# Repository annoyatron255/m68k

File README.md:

# m68k
A [Motorola 68000](https://en.wikipedia.org/wiki/Motorola_68000) computer. It uses a Lattice FPGA to control the CPU and interface with the peripherals. It is designed to be standalone, with a PS/2 port for input and a VGA port for display output. 
## Contributors
* [Avery Bartnik](https://github.com/Jythonscript)
  * [Assembly Programming](https://github.com/annoyatron255/m68k/blob/master/src/init.s)
  * README
* [Erik Duxstad](https://github.com/eduxstad)
  * Schematic
  * PCB Layout
  * Ordering PCB
* [Jack Sweeney](https://github.com/annoyatron255)
  * Schematic
  * Assembly Programming
  * FPGA Verilog
  * Simulation
* [Michael Wagner](https://github.com/MDW01)
  * Schematic
  * PCB Layout
  * Ordering Parts
## What We Did
1. Design schematic for 68000 computer
2. Design and layout the PCB
3. Order the PCB and parts
4. Wrote Verilog HDL for the FPGA
5. Set up a RTL simulator for the whole computer design
6. Wrote an assembly program in the simulator that displays text using the serial port
## What We Will Do
1. Solder the parts to the PCB
2. Synthesize the verilog and flash to SPI Flash to configure FPGA
3. Interface with the board via the serial port
4. Run programs on real hardware!
## Long-Term Improvements
1. Enable on-board SRAM
2. Configure toolchain to allow for C programming
3. Add scheduling interrupt
4. Install Linux
5. Set up VGA peripheral
6. Set up PS/2 peripheral
7. Set up SD Card peripheral
8. Make MMU on FPGA for Linux
## Gallery
### PCB

### PCB Layout 

### FPGA

### SRAM

### Schematic

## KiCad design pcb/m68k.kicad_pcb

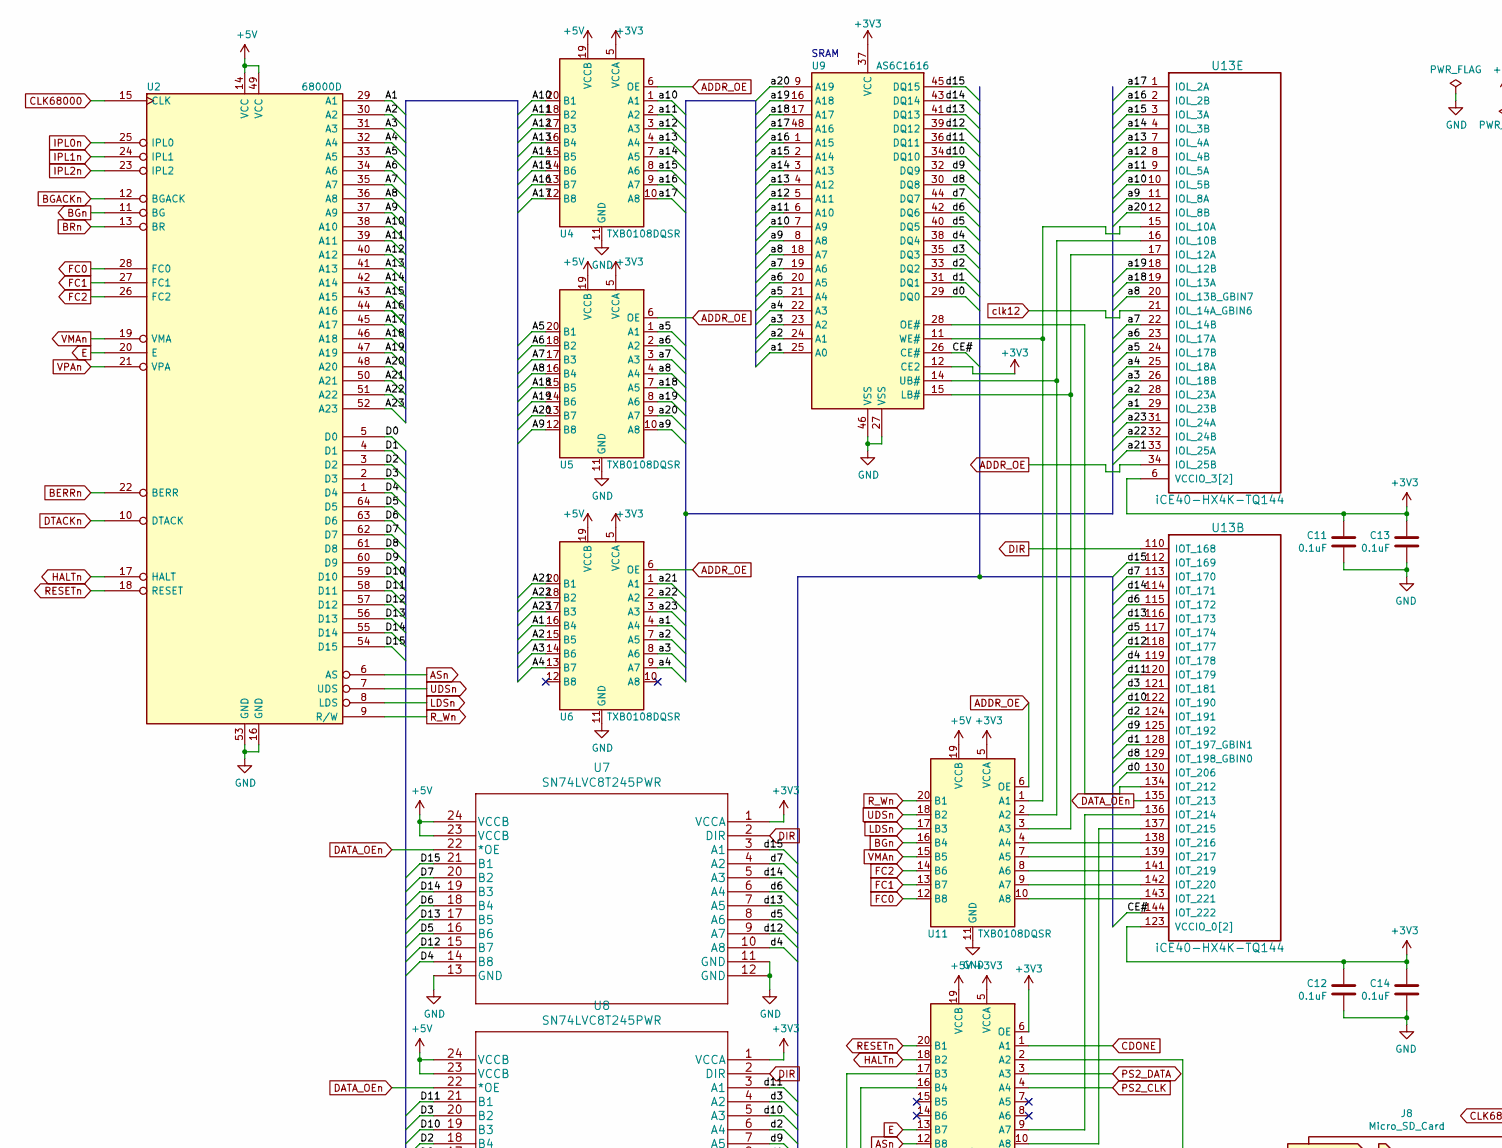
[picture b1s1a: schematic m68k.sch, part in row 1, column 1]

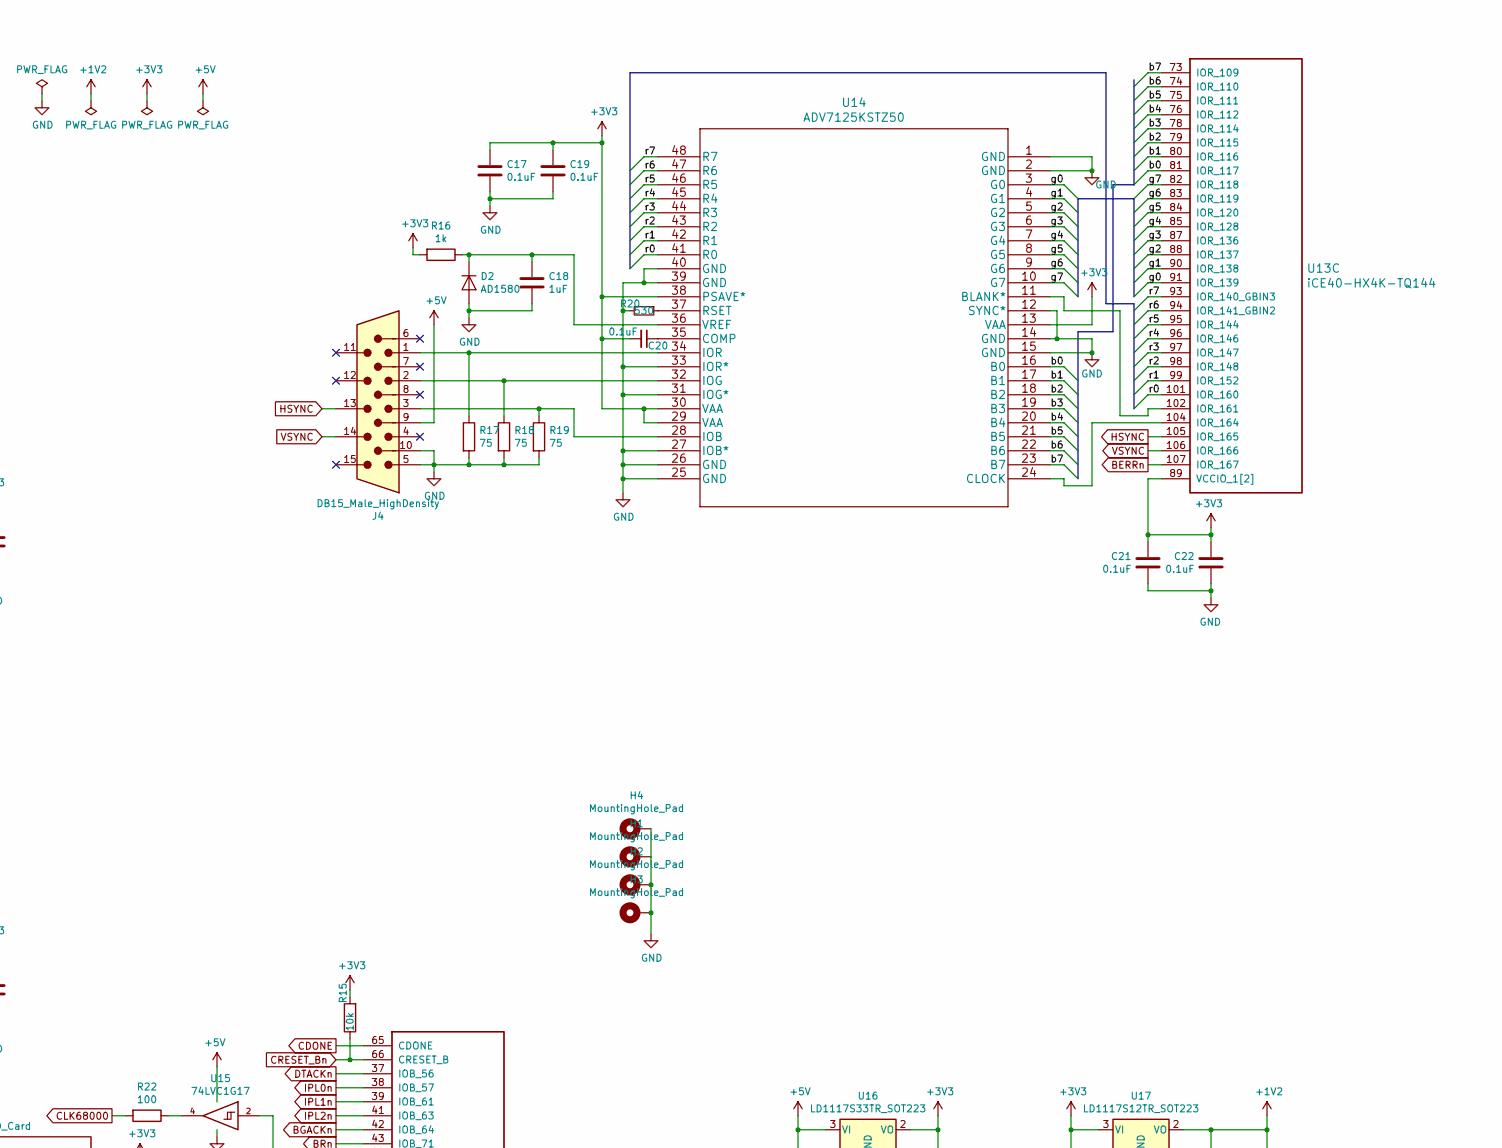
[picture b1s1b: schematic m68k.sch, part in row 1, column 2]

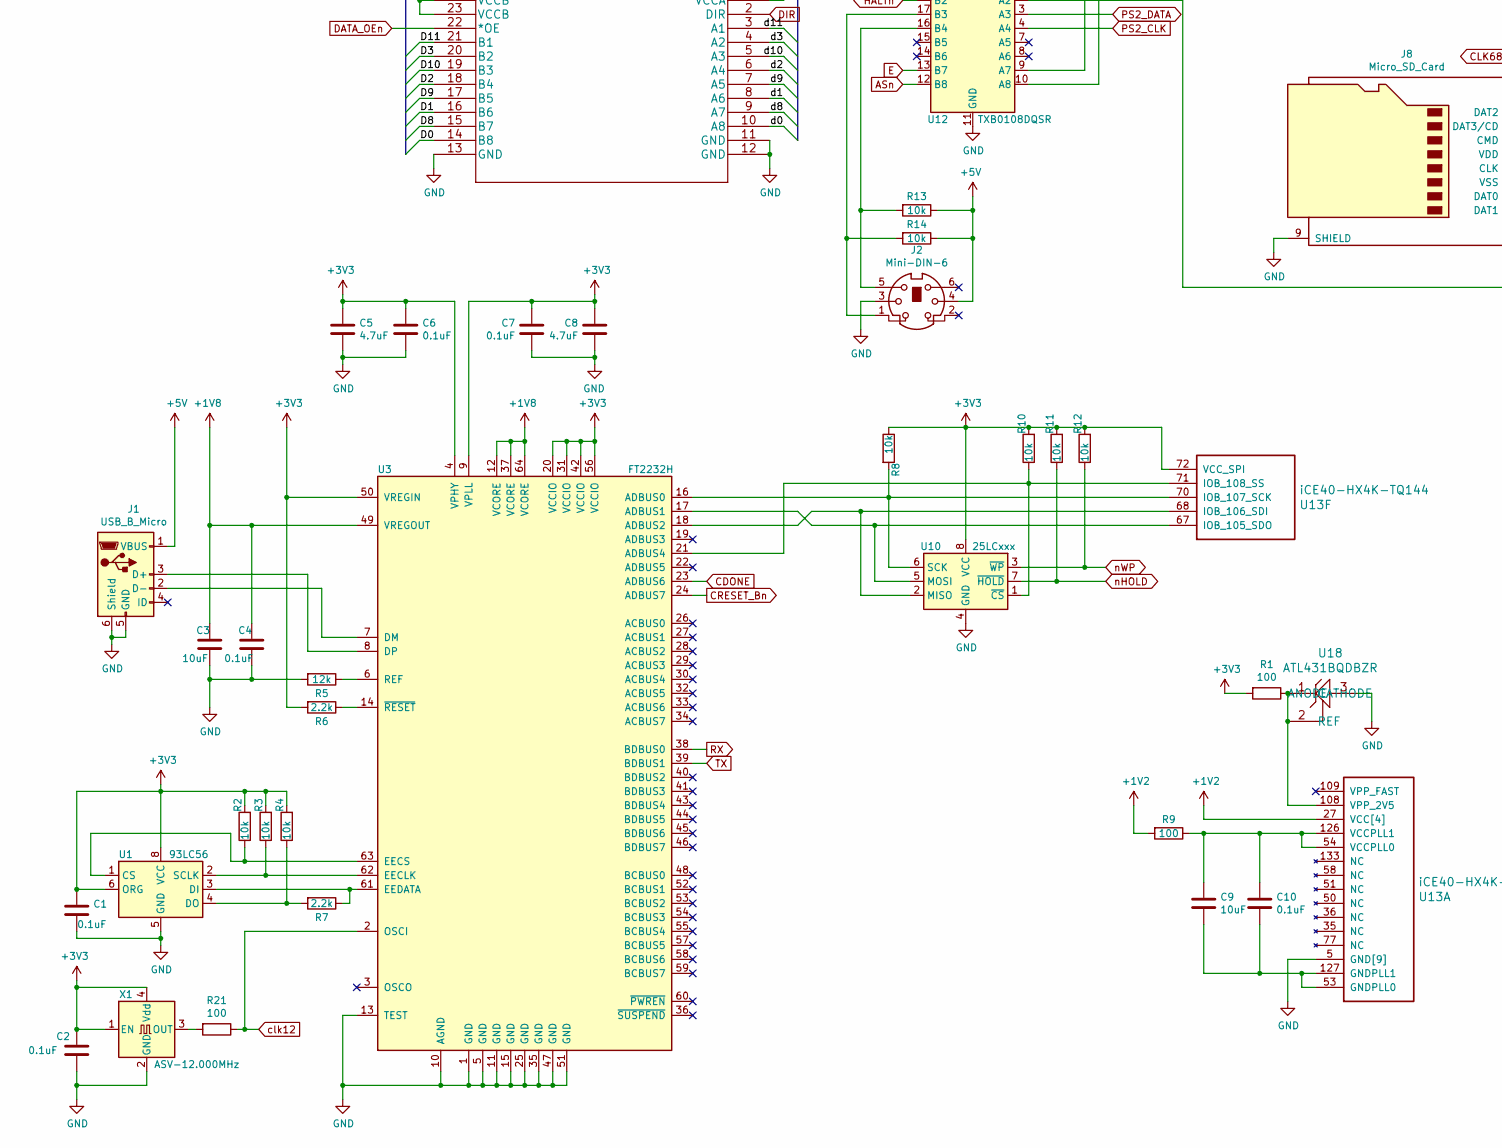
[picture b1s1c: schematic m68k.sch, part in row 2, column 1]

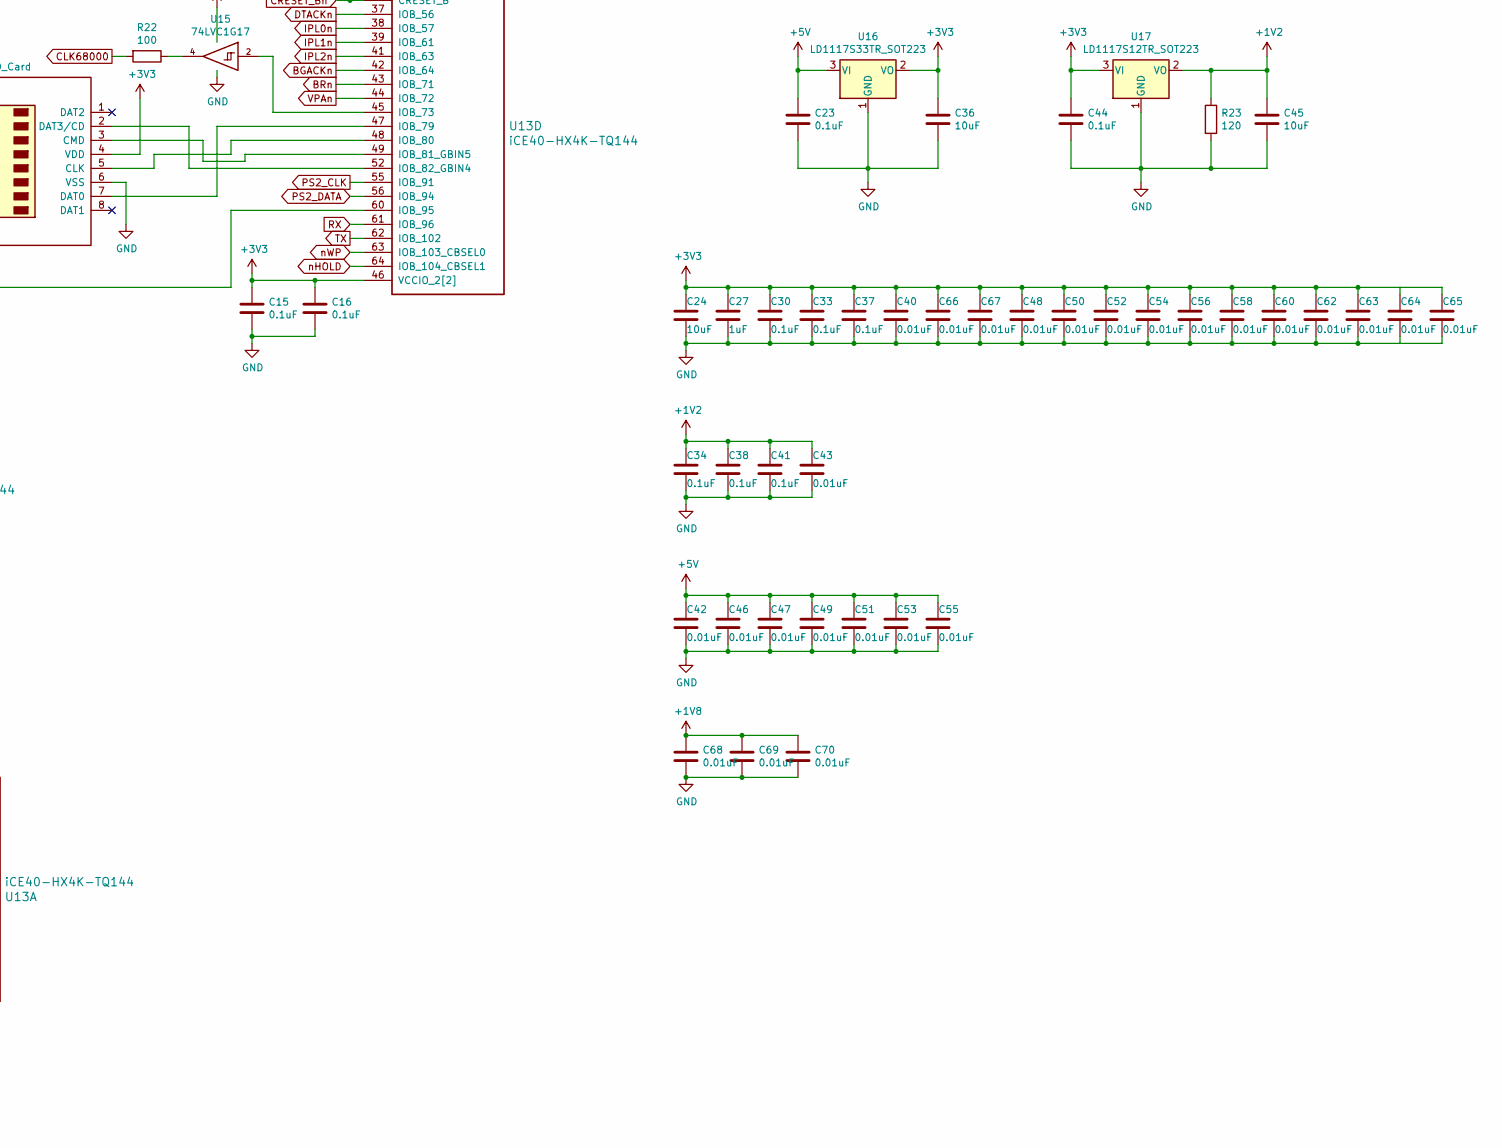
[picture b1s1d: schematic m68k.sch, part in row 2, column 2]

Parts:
C1, C2, C4, C6, C7, C10, C11, C12, C13, C14, C15, C16, C17, C19, C20, C21, C22, C23, C30, C33, C34, C37, C38, C41, C44: 0.1uF; C_0603_1608Metric
C3, C9, C24, C36, C45: 10uF; C_0603_1608Metric
C5, C8: 4.7uF; C_0603_1608Metric
C18, C27: 1uF; C_0603_1608Metric
C40, C42, C43, C46, C47, C48, C49, C50, C51, C52, C53, C54, C55, C56, C58, C60, C62, C63, C64, C65, C66, C67, C68, C69, C70: 0.01uF; C_0603_1608Metric
D2: AD1580; SOT-23
H1, H2, H3, H4: MountingHole_Pad; MountingHole_2.5mm_Pad
J1: USB_B_Micro; USB_Micro-B
J2: Mini-DIN-6; CUI_MD-60S
J4: DB15_Male_HighDensity; DSUB-15-HD_Female_Horizontal_P2.29x1.98mm_EdgePinOffset3.03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
J8: Micro_SD_Card; microSD_HC_Hirose_DM3AT-SF-PEJM5
R1, R9, R21, R22: 100; R_0603_1608Metric
R2, R3, R4, R8, R10, R11, R12, R13, R14, R15: 10k; R_0603_1608Metric
R5: 12k; R_0603_1608Metric
R6, R7: 2.2k; R_0603_1608Metric
R16: 1k; R_0603_1608Metric
R17, R18, R19: 75; R_0603_1608Metric
R20: 530; R_0603_1608Metric
R23: 120; R_0603_1608Metric
U1: 93LC56; SOIC-8_3.9x4.9mm_P1.27mm
U2: 68000D; DIP-64_W22.86mm_Socket_LongPads
U3: FT2232H; LQFP-64_10x10mm_P0.5mm
U4, U5, U6, U11, U12: TXB0108DQSR; USON-20_2x4mm_P0.4mm
U7, U8: SN74LVC8T245PWR; TSSOP-24_4.4x7.8mm_P0.65mm
U9: AS6C1616; TSOP-I-48_18.4x12mm_P0.5mm
U10: 25LCxxx; SOIC-8_3.9x4.9mm_P1.27mm
U13: iCE40-HX4K-TQ144; TQFP-144_20x20mm_P0.5mm
U14: ADV7125KSTZ50; LQFP-48_7x7mm_P0.5mm
U15: 74LVC1G17; SOT-23-5
U16: LD1117S33TR_SOT223; SOT-223-3_TabPin2
U17: LD1117S12TR_SOT223; SOT-223-3_TabPin2
U18: ATL431BQDBZR; SOT-23
X1: ASV-12.000MHz; Oscillator_SMD_Abracon_ASV-4Pin_7.0x5.1mm

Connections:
+1V2: C34.1, C38.1, C41.1, C43.1, C45.1, R9.2, R23.1, U13.27 (VCC[4]), U13.40 (VCC[4]), U13.92 (VCC[4]), U13.111 (VCC[4]), U17.2 (VO)
+1V8: C3.1, C4.1, C68.1, C69.1, C70.1, U3.12 (VCORE), U3.37 (VCORE), U3.49 (VREGOUT), U3.64 (VCORE)
+3V3: C1.1, C2.1, C5.1, C6.1, C7.1, C8.1, C11.1, C12.1, C13.1, C14.1, C15.1, C16.1, C17.1, C19.1, C20.2, C21.1, C22.1, C24.1, C27.1, C30.1, C33.1, C36.1, C37.1, C40.1, C44.1, C48.1, C50.1, C52.1, C54.1, C56.1, C58.1, C60.1, C62.1, C63.1, C64.1, C65.1, C66.1, C67.1, J8.4 (VDD), R1.2, R2.2, R3.2, R4.2, R6.2, R8.1, R10.2, R11.2, R12.2, R15.2, R16.2, U1.6 (ORG), U1.8 (VCC), U3.4 (VPHY), U3.9 (VPLL), U3.20 (VCCIO), U3.31 (VCCIO), U3.42 (VCCIO), U3.50 (VREGIN), U3.56 (VCCIO), U4.5 (VCCA), U5.5 (VCCA), U6.5 (VCCA), U7.1 (VCCA), U8.1 (VCCA), U9.12 (CE2), U9.37 (VCC), U10.8 (VCC), U11.5 (VCCA), U12.5 (VCCA), U12.6 (OE), U13.6 (VCCIO_3[2]), U13.30 (VCCIO_3[2]), U13.46 (VCCIO_2[2]), U13.57 (VCCIO_2[2]), U13.72 (VCC_SPI), U13.89 (VCCIO_1[2]), U13.100 (VCCIO_1[2]), U13.123 (VCCIO_0[2]), U13.131 (VCCIO_0[2]), U14.13 (VAA), U14.29 (VAA), U14.30 (VAA), U14.38 (PSAVE*), U16.2 (VO), U17.3 (VI), X1.1 (EN), X1.4 (Vdd)
+5V: C23.1, C42.1, C46.1, C47.1, C49.1, C51.1, C53.1, C55.1, J1.1 (VBUS), J2.4, J4.9, R13.1, R14.1, U2.14 (VCC), U2.49 (VCC), U4.19 (VCCB), U5.19 (VCCB), U6.19 (VCCB), U7.23 (VCCB), U7.24 (VCCB), U8.23 (VCCB), U8.24 (VCCB), U11.19 (VCCB), U12.19 (VCCB), U15.5 (VCC), U16.3 (VI)
/A1: U2.29 (A1), U6.16 (B4)
/A2: U2.30 (A2), U6.15 (B5)
/A3: U2.31 (A3), U6.14 (B6)
/A4: U2.32 (A4), U6.13 (B7)
/A5: U2.33 (A5), U5.20 (B1)
/A6: U2.34 (A6), U5.18 (B2)
/A7: U2.35 (A7), U5.17 (B3)
/A8: U2.36 (A8), U5.16 (B4)
/A9: U2.37 (A9), U5.12 (B8)
/A10: U2.38 (A10), U4.20 (B1)
/A11: U2.39 (A11), U4.18 (B2)
/A12: U2.40 (A12), U4.17 (B3)
/A13: U2.41 (A13), U4.16 (B4)
/A14: U2.42 (A14), U4.15 (B5)
/A15: U2.43 (A15), U4.14 (B6)
/A16: U2.44 (A16), U4.13 (B7)
/A17: U2.45 (A17), U4.12 (B8)
/A18: U2.46 (A18), U5.15 (B5)
/A19: U2.47 (A19), U5.14 (B6)
/A20: U2.48 (A20), U5.13 (B7)
/A21: U2.50 (A21), U6.20 (B1)
/A22: U2.51 (A22), U6.18 (B2)
/A23: U2.52 (A23), U6.17 (B3)
/CE#: U9.26 (CE#), U13.144 (IOT_222)
/D0: U2.5 (D0), U8.14 (B8)
/D1: U2.4 (D1), U8.16 (B6)
/D2: U2.3 (D2), U8.18 (B4)
/D3: U2.2 (D3), U8.20 (B2)
/D4: U2.1 (D4), U7.14 (B8)
/D5: U2.64 (D5), U7.16 (B6)
/D6: U2.63 (D6), U7.18 (B4)
/D7: U2.62 (D7), U7.20 (B2)
/D8: U2.61 (D8), U8.15 (B7)
/D9: U2.60 (D9), U8.17 (B5)
/D10: U2.59 (D10), U8.19 (B3)
/D11: U2.58 (D11), U8.21 (B1)
/D12: U2.57 (D12), U7.15 (B7)
/D13: U2.56 (D13), U7.17 (B5)
/D14: U2.55 (D14), U7.19 (B3)
/D15: U2.54 (D15), U7.21 (B1)
/a1: U6.4 (A4), U9.25 (A0), U13.29 (IOL_23B)
/a2: U6.7 (A5), U9.24 (A1), U13.28 (IOL_23A)
/a3: U6.8 (A6), U9.23 (A2), U13.26 (IOL_18B)
/a4: U6.9 (A7), U9.22 (A3), U13.25 (IOL_18A)
/a5: U5.1 (A1), U9.21 (A4), U13.24 (IOL_17B)
/a6: U5.2 (A2), U9.20 (A5), U13.23 (IOL_17A)
/a7: U5.3 (A3), U9.19 (A6), U13.22 (IOL_14B)
/a8: U5.4 (A4), U9.18 (A7), U13.20 (IOL_13B_GBIN7)
/a9: U5.10 (A8), U9.8 (A8), U13.11 (IOL_8A)
/a10: U4.1 (A1), U9.7 (A9), U13.10 (IOL_5B)
/a11: U4.2 (A2), U9.6 (A10), U13.9 (IOL_5A)
/a12: U4.3 (A3), U9.5 (A11), U13.8 (IOL_4B)
/a13: U4.4 (A4), U9.4 (A12), U13.7 (IOL_4A)
/a14: U4.7 (A5), U9.3 (A13), U13.4 (IOL_3B)
/a15: U4.8 (A6), U9.2 (A14), U13.3 (IOL_3A)
/a16: U4.9 (A7), U9.1 (A15), U13.2 (IOL_2B)
/a17: U4.10 (A8), U9.48 (A16), U13.1 (IOL_2A)
/a18: U5.7 (A5), U9.17 (A17), U13.19 (IOL_13A)
/a19: U5.8 (A6), U9.16 (A18), U13.18 (IOL_12B)
/a20: U5.9 (A7), U9.9 (A19), U13.12 (IOL_8B)
/a21: U6.1 (A1), U13.33 (IOL_25A)
/a22: U6.2 (A2), U13.32 (IOL_24B)
/a23: U6.3 (A3), U13.31 (IOL_24A)
/b0: U13.81 (IOR_117), U14.16 (B0)
/b1: U13.80 (IOR_116), U14.17 (B1)
/b2: U13.79 (IOR_115), U14.18 (B2)
/b3: U13.78 (IOR_114), U14.19 (B3)
/b4: U13.76 (IOR_112), U14.20 (B4)
/b5: U13.75 (IOR_111), U14.21 (B5)
/b6: U13.74 (IOR_110), U14.22 (B6)
/b7: U13.73 (IOR_109), U14.23 (B7)
/d0: U8.10 (A8), U9.29 (DQ0), U13.130 (IOT_206)
/d1: U8.8 (A6), U9.31 (DQ1), U13.128 (IOT_197_GBIN1)
/d2: U8.6 (A4), U9.33 (DQ2), U13.124 (IOT_191)
/d3: U8.4 (A2), U9.35 (DQ3), U13.121 (IOT_181)
/d4: U7.10 (A8), U9.38 (DQ4), U13.119 (IOT_178)
/d5: U7.8 (A6), U9.40 (DQ5), U13.117 (IOT_174)
/d6: U7.6 (A4), U9.42 (DQ6), U13.115 (IOT_172)
/d7: U7.4 (A2), U9.44 (DQ7), U13.113 (IOT_170)
/d8: U8.9 (A7), U9.30 (DQ8), U13.129 (IOT_198_GBIN0)
/d9: U8.7 (A5), U9.32 (DQ9), U13.125 (IOT_192)
/d10: U8.5 (A3), U9.34 (DQ10), U13.122 (IOT_190)
/d11: U8.3 (A1), U9.36 (DQ11), U13.120 (IOT_179)
/d12: U7.9 (A7), U9.39 (DQ12), U13.118 (IOT_177)
/d13: U7.7 (A5), U9.41 (DQ13), U13.116 (IOT_173)
/d14: U7.5 (A3), U9.43 (DQ14), U13.114 (IOT_171)
/d15: U7.3 (A1), U9.45 (DQ15), U13.112 (IOT_169)
/g0: U13.91 (IOR_139), U14.3 (G0)
/g1: U13.90 (IOR_138), U14.4 (G1)
/g2: U13.88 (IOR_137), U14.5 (G2)
/g3: U13.87 (IOR_136), U14.6 (G3)
/g4: U13.85 (IOR_128), U14.7 (G4)
/g5: U13.84 (IOR_120), U14.8 (G5)
/g6: U13.83 (IOR_119), U14.9 (G6)
/g7: U13.82 (IOR_118), U14.10 (G7)
/r0: U13.101 (IOR_160), U14.41 (R0)
/r1: U13.99 (IOR_152), U14.42 (R1)
/r2: U13.98 (IOR_148), U14.43 (R2)
/r3: U13.97 (IOR_147), U14.44 (R3)
/r4: U13.96 (IOR_146), U14.45 (R4)
/r5: U13.95 (IOR_144), U14.46 (R5)
/r6: U13.94 (IOR_141_GBIN2), U14.47 (R6)
/r7: U13.93 (IOR_140_GBIN3), U14.48 (R7)
ADDR_OE: U4.6 (OE), U5.6 (OE), U6.6 (OE), U11.6 (OE), U13.34 (IOL_25B)
ASn: U2.6 (AS), U12.12 (B8)
BERRn: U2.22 (BERR), U13.107 (IOR_167)
BGACKn: U2.12 (BGACK), U13.42 (IOB_64)
BGn: U2.11 (BG), U11.16 (B4)
BRn: U2.13 (BR), U13.43 (IOB_71)
CDONE: U3.23 (ADBUS6), U12.1 (A1), U13.65 (CDONE)
CLK68000: R22.2, U2.15 (CLK)
CRESET_Bn: R15.1, U3.24 (ADBUS7), U13.66 (CRESET_B)
DATA_OEn: U7.22 (*OE), U8.22 (*OE), U13.135 (IOT_213)
DIR: U7.2 (DIR), U8.2 (DIR), U13.110 (IOT_168)
DTACKn: U2.10 (DTACK), U13.37 (IOB_56)
E: U2.20 (E), U12.13 (B7)
FC0: U2.28 (FC0), U11.12 (B8)
FC1: U2.27 (FC1), U11.13 (B7)
FC2: U2.26 (FC2), U11.14 (B6)
GND: C1.2, C2.2, C3.2, C4.2, C5.2, C6.2, C7.2, C8.2, C11.2, C12.2, C13.2, C14.2, C15.2, C16.2, C17.2, C18.2, C19.2, C21.2, C22.2, C23.2, C24.2, C27.2, C30.2, C33.2, C34.2, C36.2, C37.2, C38.2, C40.2, C41.2, C42.2, C43.2, C44.2, C45.2, C46.2, C47.2, C48.2, C49.2, C50.2, C51.2, C52.2, C53.2, C54.2, C55.2, C56.2, C58.2, C60.2, C62.2, C63.2, C64.2, C65.2, C66.2, C67.2, C68.2, C69.2, C70.2, D2.2 (A), H1.1, H2.1, H3.1, H4.1, J1.5 (GND), J1.6 (Shield), J2.3, J4.5, J4.10, J8.6 (VSS), J8.9 (SHIELD), R5.2, R17.2, R18.2, R19.2, R20.2, R23.2, U1.5 (GND), U2.16 (GND), U2.53 (GND), U3.1 (GND), U3.5 (GND), U3.10 (AGND), U3.11 (GND), U3.13 (TEST), U3.15 (GND), U3.25 (GND), U3.35 (GND), U3.47 (GND), U3.51 (GND), U4.11 (GND), U5.11 (GND), U6.11 (GND), U7.11 (GND), U7.12 (GND), U7.13 (GND), U8.11 (GND), U8.12 (GND), U8.13 (GND), U9.27 (VSS), U9.46 (VSS), U10.4 (GND), U11.11 (GND), U12.11 (GND), U13.5 (GND[9]), U13.13 (GND[9]), U13.14 (GND[9]), U13.59 (GND[9]), U13.69 (GND[9]), U13.86 (GND[9]), U13.103 (GND[9]), U13.132 (GND[9]), U13.140 (GND[9]), U14.1 (GND), U14.2 (GND), U14.12 (SYNC*), U14.14 (GND), U14.15 (GND), U14.25 (GND), U14.26 (GND), U14.27 (IOB*), U14.31 (IOG*), U14.33 (IOR*), U14.39 (GND), U14.40 (GND), U15.3 (GND), U16.1 (GND), U17.1 (GND), U18.3 (ANODE), X1.2 (GND)
HALTn: U2.17 (HALT), U12.18 (B2)
HSYNC: J4.13, U13.105 (IOR_165)
IPL0n: U2.25 (IPL0), U13.38 (IOB_57)
IPL1n: U2.24 (IPL1), U13.39 (IOB_61)
IPL2n: U2.23 (IPL2), U13.41 (IOB_63)
LDSn: U2.8 (LDS), U11.17 (B3)
unnamed: C9.1, C10.1, R9.1, U13.54 (VCCPLL0), U13.126 (VCCPLL1)
unnamed: C9.2, C10.2, U13.53 (GNDPLL0), U13.127 (GNDPLL1)
unnamed: C18.1, D2.1 (K), R16.1, U14.36 (VREF)
unnamed: C20.1, U14.35 (COMP)
unnamed: J1.2 (D-), U3.7 (DM)
unnamed: J1.3 (D+), U3.8 (DP)
unnamed: J2.1, R14.2, U12.17 (B3)
unnamed: J2.5, R13.2, U12.16 (B4)
unnamed: J4.1, R17.1, U14.34 (IOR)
unnamed: J4.2, R18.1, U14.32 (IOG)
unnamed: J4.3, R19.1, U14.28 (IOB)
unnamed: J8.2 (DAT3/CD), U13.52 (IOB_82_GBIN4)
unnamed: J8.3 (CMD), U13.49 (IOB_81_GBIN5)
unnamed: J8.5 (CLK), U13.48 (IOB_80)
unnamed: J8.7 (DAT0), U13.47 (IOB_79)
unnamed: R1.1, U13.108 (VPP_2V5), U18.1 (CATHODE), U18.2 (REF)
unnamed: R2.1, U1.1 (CS), U3.63 (EECS)
unnamed: R3.1, U1.2 (SCLK), U3.62 (EECLK)
unnamed: R4.1, R7.2, U1.4 (DO)
unnamed: R5.1, U3.6 (REF)
unnamed: R6.1, U3.14 (~RESET)
unnamed: R7.1, U1.3 (DI), U3.61 (EEDATA)
unnamed: R8.2, U3.16 (ADBUS0), U10.6 (SCK), U13.70 (IOB_107_SCK)
unnamed: R10.1, U3.21 (ADBUS4), U10.1 (~CS), U13.71 (IOB_108_SS)
unnamed: R20.1, U14.37 (RSET)
unnamed: R21.2, X1.3 (OUT)
unnamed: R22.1, U15.4
unnamed: U3.18 (ADBUS2), U10.2 (MISO), U13.68 (IOB_106_SDI)
unnamed: U3.17 (ADBUS1), U10.5 (MOSI), U13.67 (IOB_105_SDO)
unnamed: U9.11 (WE#), U11.1 (A1), U13.15 (IOL_10A)
unnamed: U9.14 (UB#), U11.2 (A2), U13.16 (IOL_10B)
unnamed: U9.15 (LB#), U11.3 (A3), U13.17 (IOL_12A)
unnamed: U11.4 (A4), U13.138 (IOT_216)
unnamed: U11.7 (A5), U13.139 (IOT_217)
unnamed: U11.8 (A6), U13.141 (IOT_219)
unnamed: U11.9 (A7), U13.142 (IOT_220)
unnamed: U11.10 (A8), U13.143 (IOT_221)
unnamed: U12.2 (A2), U13.60 (IOB_95)
unnamed: U12.9 (A7), U13.136 (IOT_214)
unnamed: U12.10 (A8), U13.137 (IOT_215)
unnamed: U13.45 (IOB_73), U15.2
unnamed: U13.102 (IOR_161), U14.11 (BLANK*)
unnamed: U13.104 (IOR_164), U14.24 (CLOCK)
unnamed: U9.28 (OE#), U13.134 (IOT_212)
PS2_CLK: U12.4 (A4), U13.55 (IOB_91)
PS2_DATA: U12.3 (A3), U13.56 (IOB_94)
RESETn: U2.18 (RESET), U12.20 (B1)
RX: U3.38 (BDBUS0), U13.61 (IOB_96)
R_Wn: U2.9 (R/W), U11.20 (B1)
TX: U3.39 (BDBUS1), U13.62 (IOB_102)
UDSn: U2.7 (UDS), U11.18 (B2)
VMAn: U2.19 (VMA), U11.15 (B5)
VPAn: U2.21 (VPA), U13.44 (IOB_72)
VSYNC: J4.14, U13.106 (IOR_166)
clk12: R21.1, U3.2 (OSCI), U13.21 (IOL_14A_GBIN6)
nHOLD: R11.1, U10.7 (~HOLD), U13.64 (IOB_104_CBSEL1)
nWP: R12.1, U10.3 (~WP), U13.63 (IOB_103_CBSEL0)

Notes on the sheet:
SRAM

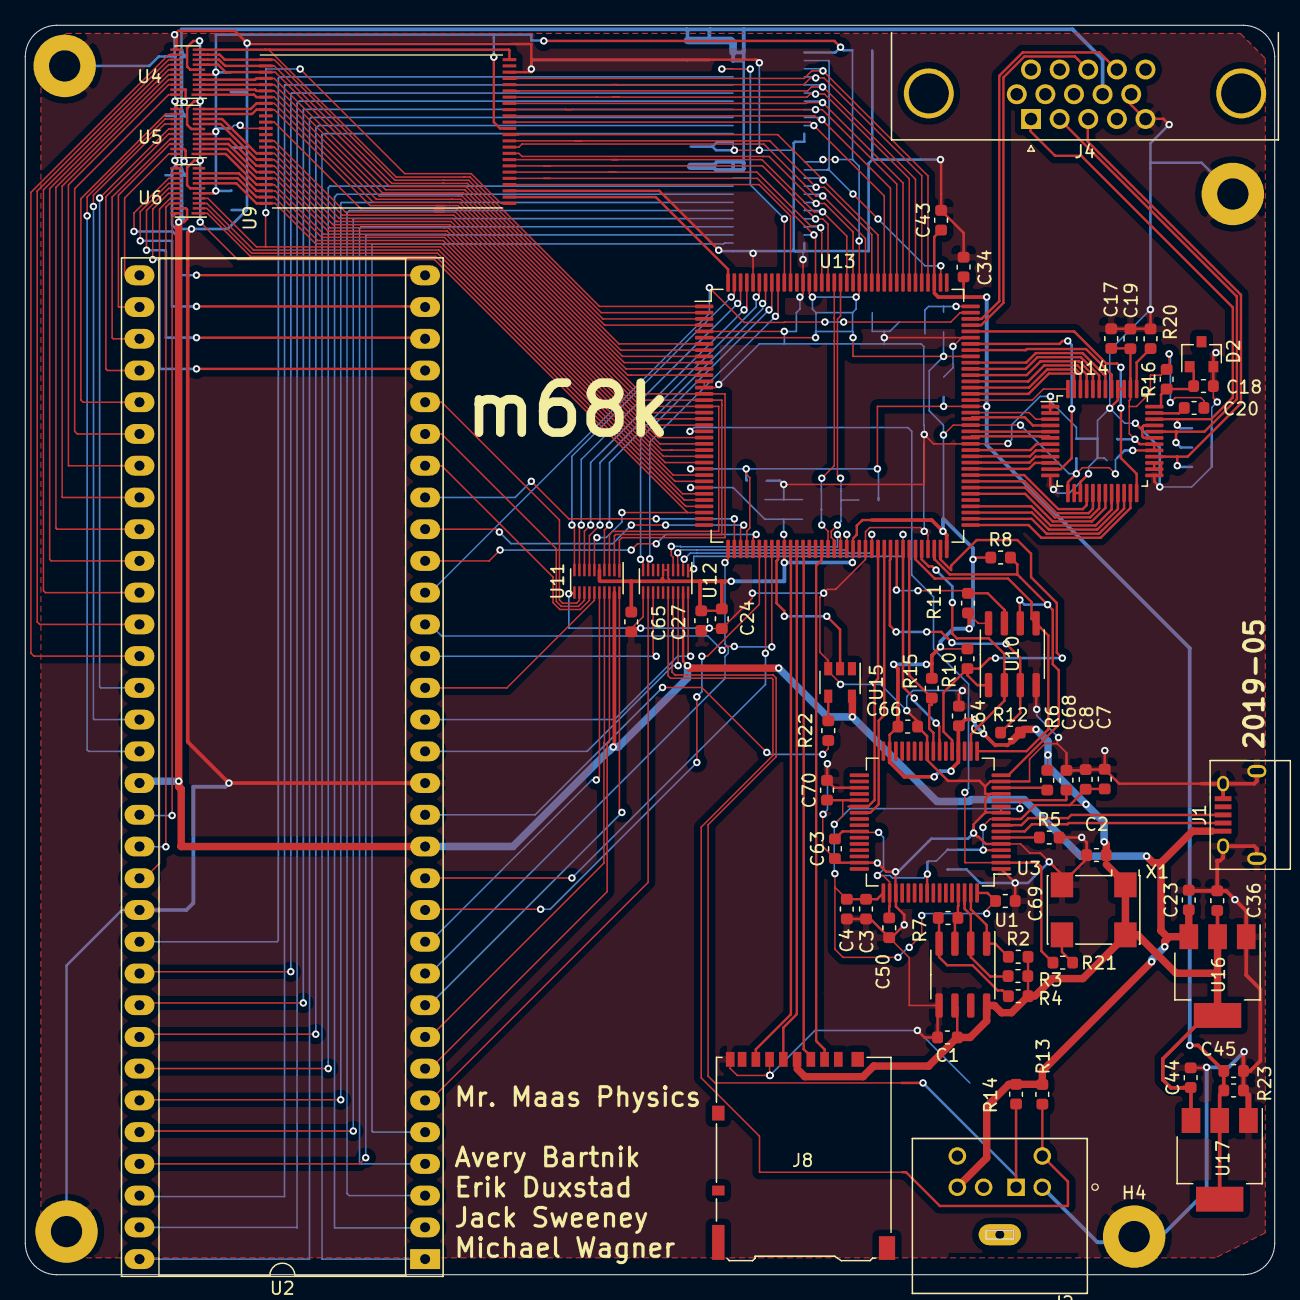
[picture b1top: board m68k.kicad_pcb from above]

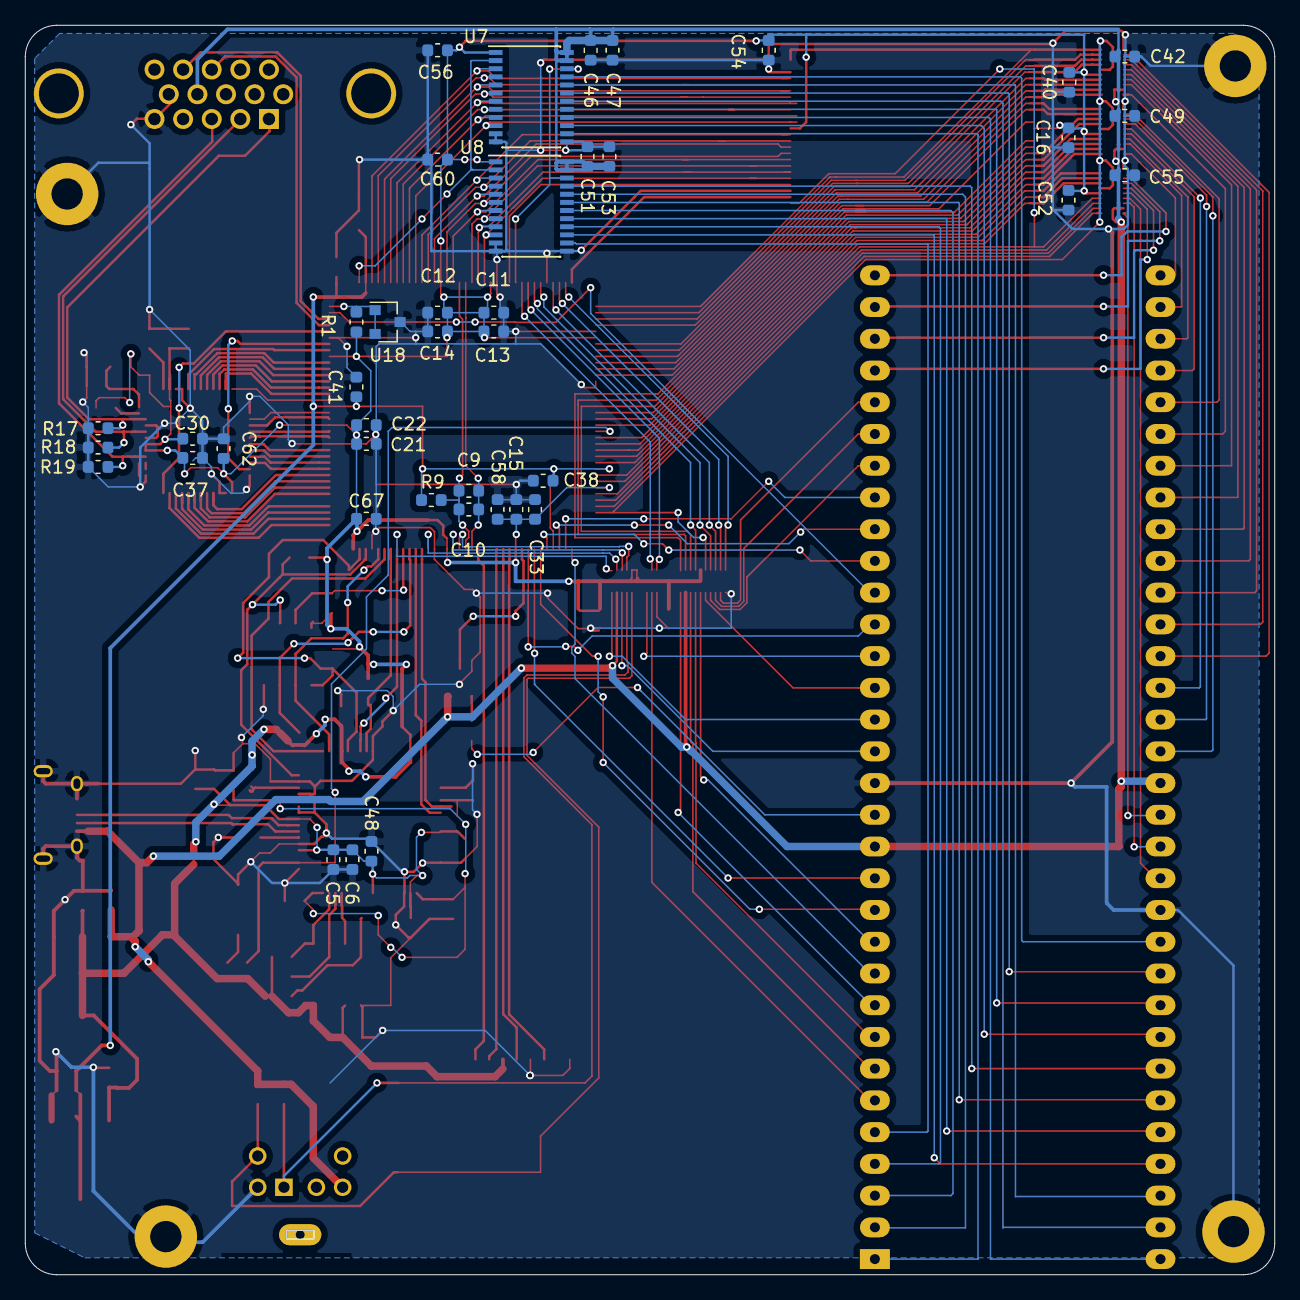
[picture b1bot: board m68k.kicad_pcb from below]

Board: 2 copper layers, 100.0 x 100.0 mm, 110 parts (41 on the bottom side), 187 nets.

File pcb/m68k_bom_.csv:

Component,Description,Value,Footprint,Quantity Per PCB,Digikey,Ordered ,,,
1,Unpolarized capacitor,10000 pF,0603,25,_1276-1132-1-ND_,,,,
2,Unpolarized capacitor,0.1uF,0603,25,_1276-1006-1-ND_,,,,
3,Unpolarized capacitor,10uF,0603,5,_1276-1192-1-ND_,,,,
4,Unpolarized capacitor,1uF,0603,2,1276-1102-1-ND_,,,,
5,Unpolarized capacitor,4.7uF,0603,2,_1276-1044-1-ND_,,,,
6,Diode,AD1580,SOT-23,1,_AD1580ARTZ-REEL7CT-ND_,,,,
7,Micro SD Card Socket,Micro_SD_Card,DM3AT-SF-PEJM5,1,_HR1964CT-ND_,,,,
8,Mini-DIN-6,Mini-DIN-6,CUI_MD-60S,1,_CP-2460-ND_,,,,
9,USB_B_Micro,USB_B_Micro,USB_Micro-B,1,_609-4618-1-ND_,,,,
10,Resistor,100,0603,4,311-100HRCT-ND,,,,
11,Resistor,10k,0603,10,N/A,0,,,
12,Resistor,120,0603,1,311-120HRCT-ND,,,,
13,Resistor,1k,0603,1,N/A,0,,,
14,Resistor,2.2k,0603,3,311-2.20KHRCT-ND,,,,
15,Resistor,530,0603,1,_311-536HRCT-ND_,,,,
16,Resistor,75,0603,3,311-75.0HRCT-ND,,,,
17,"SPI Serial EEPROM, DIP-8/SOIC-8/TSSOP-8",25LCxxx,SOIC-8_3.9x4.9mm_P1.27mm,1,_W25Q128JVSIMCT-ND_,,,,
18,68000D,68000D,DIP-64_W22.86mm_Socket_LongPads,1,N/A,0,,,
19,"Single Schmitt Buffer Gate, Low-Voltage CMOS",74LVC1G17,SOT-23-5,1,_296-35948-1-ND_,,,,
20,"Serial EEPROM, 93 Series, with ORG Pin, 2.5V, DIP-8/SOIC-8",93LC56,SOIC-8_3.9x4.9mm_P1.27mm,1,_93LC56BT-I/SNCT-ND_,,,,
21,,ADV7125KSTZ50,LQFP-48_7x7mm_P0.5mm,1,_ADV7125KSTZ50-ND_,,,,
22,,AS6C1616,TSOP-I-48_18.4x12mm_P0.5mm,1,_1450-1022-ND_,,,,
23,,ATL431BQDBZR,SOT-23,1,_296-44371-1-ND_,,,,
24,"FT2232Hx, Hi Speed Double Channel USB UART/FIFO, LQFP/QFN-64",FT2232H,LQFP-64_10x10mm_P0.5mm,1,_768-1347-ND_,,,,
25,"800mA Fixed Low Drop Positive Voltage Regulator, Fixed Output 1.2V, SOT-223",LD1117S12TR_SOT223,SOT-223-3_TabPin2,1,_497-4240-1-ND_,,,,
26,"800mA Fixed Low Drop Positive Voltage Regulator, Fixed Output 3.3V, SOT-223",LD1117S33TR_SOT223,SOT-223-3_TabPin2,1,_497-1242-1-ND_,,,,
27,,SN74LVC8T245PWR,TSSOP-24_4.4x7.8mm_P0.65mm,2,_296-18593-1-ND_,,,,
28,,TXB0108DQSR,USON-20_2x4mm_P0.4mm,5,_296-27217-1-ND_,,,,
29,,iCE40-HX4K-TQ144,TQFP-144_20x20mm_P0.5mm,1,_220-1572-ND_,,,,
30,"3.3V HCMOS SMD Crystal Clock Oscillator, Abracon",ASV-12.000MHz,Oscillator_SMD_Abracon_ASV-4Pin_7.0x5.1mm,1,_535-9309-1-ND_,,,,

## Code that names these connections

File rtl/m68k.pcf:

set_io clk12 21
set_io CLK68000 45

set_io addr[1] 29
set_io addr[2] 28
set_io addr[3] 26
set_io addr[4] 25
set_io addr[5] 24
set_io addr[6] 23
set_io addr[7] 22
set_io addr[8] 20
set_io addr[9] 11
set_io addr[10] 10
set_io addr[11] 9
set_io addr[12] 8
set_io addr[13] 7
set_io addr[14] 4
set_io addr[15] 3
set_io addr[16] 2
set_io addr[17] 1
set_io addr[18] 19
set_io addr[19] 18
set_io addr[20] 12
set_io addr[21] 33
set_io addr[22] 32
set_io addr[23] 31

set_io data[0] 130
set_io data[1] 128
set_io data[2] 124
set_io data[3] 121
set_io data[4] 119
set_io data[5] 117
set_io data[6] 115
set_io data[7] 113
set_io data[8] 129
set_io data[9] 125
set_io data[10] 122
set_io data[11] 120
set_io data[12] 118
set_io data[13] 116
set_io data[14] 114
set_io data[15] 112

set_io ASn 137
set_io R_Wn 15
set_io UDSn 16
set_io LDSn 17
set_io DTACKn 37

set_io BRn 43
set_io BGn 138
set_io BGACKn 42

set_io IPLn[0] 38
set_io IPLn[1] 39
set_io IPLn[2] 41

set_io FC[0] 143
set_io FC[1] 142
set_io FC[2] 141

set_io E 136
set_io VMAn 139
set_io VPAn 44

set_io BERRn 107
#set_io RESETn
set_io HALTn 60

set_io DATA_OEn 135
set_io ADDR_OE 34
set_io DIR 110

set_io RX 61
set_io TX 62

#set_io [7:0] RX_data
#set_io [7:0] TX_data
#set_io TXE
#set_io TX_read

set_io SRAM_OEn 134
set_io SRAM_CEn 144

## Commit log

2019-05-15 Add KiCAD files
2019-05-16 start schematic
2019-05-16 potential dram schematic
2019-05-17 add rtdi sd and ps2
2019-05-17 Cleanup schematic and fix errors
2019-05-17 add vga dac and start control pins
2019-05-17 Clean-up some signals
2019-05-19 Fix mostly everything
2019-05-19 Fix VBUS voltage
2019-05-19 Add various updates and import to Pcbnew
2019-05-19 Reordered U8 Pins
2019-05-20 Reorder SRAM Pins
2019-05-20 add test points and rearrange pins
    This branch needs to be checked to make sure I didn't mess anything up on the pcb. If so, you can merge it back into erik-dev, otherwise you'll have to update the schem and pcb manually
2019-05-20 Update footprints (Mini DIN for PS/2 still missing)
2019-05-20 start pcb layout
2019-05-20 update io
2019-05-20 Added board outline
2019-05-20 arrange pcb
2019-05-20 switch to micro sd
2019-05-20 fix vga pinout
2019-05-20 add ps/2
2019-05-20 change to 200x100
2019-05-20 Add initial files for verilog
2019-05-21 continue pcb layout
2019-05-21 add autorouter attempt
2019-05-21 routing
2019-05-21 continue routing
2019-05-21 Add initial build utils for rom
2019-05-21 Add darwin tools and update Makefile
2019-05-21 good luck michael
2019-05-21 Add base verilog (untested)
2019-05-22 SAVE ME -Kicad
2019-05-22 Battle Bus
2019-05-22 PINS
2019-05-22 Create first successful simulation
2019-05-22 We should have used EAGLE
2019-05-22 vga struggle
2019-05-22 WHERE'S ROUTING?
2019-05-22 pcb stuff
2019-05-22 Cleaned up CAPS
2019-05-22 Repin
2019-05-22 SRAM!!!!
2019-05-22 SRAM????
2019-05-22 clean up pins
2019-05-22 SAVE
2019-05-22 Home
2019-05-22 Add write support
2019-05-23 I finally broke something
2019-05-23 Add basic terminal support
2019-05-23 almost finish routing
2019-05-23 silkscreen pass
2019-05-23 Done?
2019-05-23 Erik
2019-05-23 vanity
2019-05-23 add README.md
2019-05-23 Finished
2019-05-23 Prepare for switching to Verilator
2019-05-24 pre pour
2019-05-24 ordered
2019-05-24 Add first functional verilator simulation
2019-05-24 add Hello World program
2019-05-24 Add interactivity to simulation
2019-05-24 Correct memory map error
2019-05-24 Add carriage return in Hello World for ncurses
2019-05-24 Modify input code
2019-05-27 Switch to proper UARTs transitioning to real hardware
2019-05-28 add contributors and project overview to README.md
2019-05-28 Add contributor tasks
2019-05-28 add future plans to README.md
2019-05-28 Update schematic PDF
2019-05-28 add gallery to README.md
2019-05-28 use relative paths for images in README.md
2019-05-28 Add pcb layout editor images
2019-05-28 add PCB layout to gallery
2019-05-28 fix duplicate image in gallery
2019-05-28 Modify "What We Did"
2019-05-28 add schematic to gallery
2019-05-28 add link to assembly file
2019-05-28 Correct path for boot_rom
2019-05-28 format readme
2019-05-28 typo
2019-05-28 another typo
2019-05-29 Set txf_n to 1 on boot
2019-05-31 update ps/2, usb, and mounting hole.
2019-06-01 update resistor value
